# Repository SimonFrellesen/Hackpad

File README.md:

# Hackpad
This is my first ever project, it has taken me alot of time, but i finally think im done!
Its a Hackpad with inspiration from the Hackpad guide in Hackclub Blueprint.
Ive added an OLED and 2 SK6812 LEDs.

I made this project to learn and get experience. I love learning about things like PCB design and CAD design. Im interested in making more projects.

I want to give the keybinds some functions, which i havent decided yet. Probably Copy Paste and Back, and i want the LEDS to light up when i click any of the keybinds. The OLED is a starting screen.

Case:

Schematic:

PCB:

BOM

Microcontroller,1,Seeed XIAO RP2040, 3,9$ 
https://www.seeedstudio.com/XIAO-RP2040-v1-0-p-5026.html

Switches,3,MX Mechanical Switches, 3,54$
https://prototypist.net/products/in-stock-cherry-petal-switches-mx2a-10-pack?

Keycaps,3,DSA Blank Keycaps RED, 2,95$
https://spkeyboards.com/products/sp-dsa-1-space?_pos=2&_sid=1517b3abf&_ss=r

LEDs,2,SK6812 MINI-E,6,82 $
https://www.fruugo.dk/50pcs-sk6812-mini-e-rgb-similar-with-ws2812b-sk6812-3228-pixel-led-chip-individually-addressable-full-color-dc5v/p-463377372-975161187?language=en&ac=google&utm_source=google&utm_medium=paid&gclsrc=aw.ds&gad_source=1&gad_campaignid=22754370664&gclid=Cj0KCQiA4pvMBhDYARIsAGfgwvwNpXvtsZomRVqGYj1da2fajGKmsTNVzbFB5r3mlnLZWW9GODhXgWoaAosWEALw_wcB

Display,1,0.91in I2C OLED, 1,14 US$
https://www.alibaba.com/pla/091-Inch-OLED-Display-12832-Module_1601269142088.html?mark=google_shopping&biz=pla&searchText=lcd+modules&product_id=1601269142088&pcy=dk_en&src=sem_ggl&field=UG&from=sem_ggl&cmpgn=22700597011&adgrp=180785828586&fditm=&tgt=pla-295818637131&locintrst=&locphyscl=1005307&mtchtyp=&ntwrk=g&device=c&dvcmdl=&creative=759400368396&plcmnt=&plcmntcat=&aceid=&position=&gad_source=1&gad_campaignid=22700597011&gclid=Cj0KCQiA4pvMBhDYARIsAGfgwvx1X7AYZ3_Su9_hLzb9Zzgr-tyjhehcAmzHDxJittwtxviYdVgbd_4aAgNfEALw_wcB

PCB, 2$ print
https://cart.jlcpcb.com/quote?stencilLayer=2&stencilWidth=100&stencilLength=100&stencilCounts=5&plateType=1&spm=Jlcpcb.Homepage.1010

Total, 21,26$

3D printed case

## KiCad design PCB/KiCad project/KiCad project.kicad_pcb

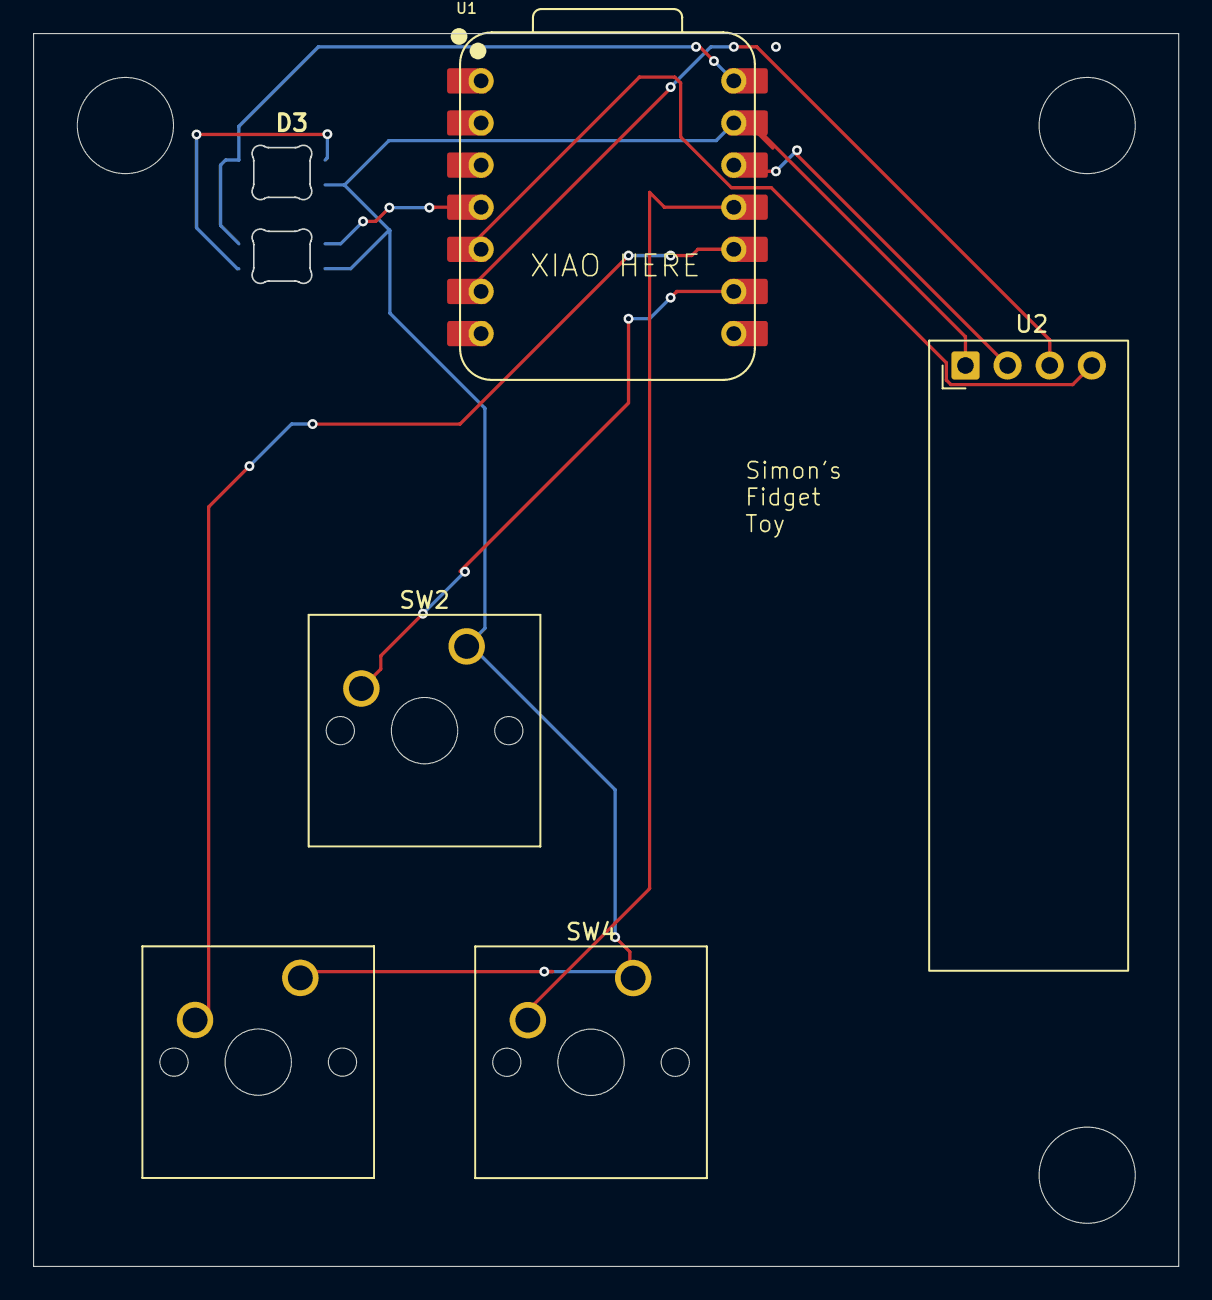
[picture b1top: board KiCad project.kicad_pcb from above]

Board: 2 copper layers, 69.0 x 74.3 mm, 7 parts (0 on the bottom side), 10 nets.

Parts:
D3, D4: SK6812MINI-E; SK6812MINI-E_fixed
SW2, SW3, SW4: SW_Push; SW_Cherry_MX_1.00u_PCB
U1: XIAO-RP2040-DIP
U2: OLED_0.91_128x32

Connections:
+5V: D3.1 (VDD), D4.1 (VDD), U1.14 (VBUS)
GND: D3.3 (VSS), D4.3 (VSS), SW2.1, SW3.1, SW4.1, U1.13 (GND), U2.1 (GND)
unnamed: D3.4 (DIN), D4.2 (DOUT)
unnamed: D4.4 (DIN), U1.4 (GPIO29/ADC3/A3)
unnamed: U1.12 (3V3), U2.2 (VCC)
unnamed: SW2.2, U1.9 (GPIO2/SCK)
unnamed: SW4.2, U1.11 (GPIO3/MOSI)
unnamed: SW3.2, U1.10 (GPIO4/MISO)
unnamed: U1.5 (GPIO6/SDA), U2.4 (SDA)
unnamed: U1.6 (GPIO7/SCL), U2.3 (SCL)

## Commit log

2026-01-30 Update README with project details and specifications
    Added project description, specifications, and images.
2026-01-30 Update README with images for case and PCB
    Added images for case, schematic, and PCB sections.
2026-01-30 Update README with BOM specifications and images
    Added specifications for BOM and case images.
2026-01-30 Update README with project specifications
    Add project specifications and BOM details
2026-02-07 Remove KiCad project job configuration file
2026-02-07 Remove duplicate keycap link from README
    Removed duplicate keycap link for clarity.
2026-02-07 Update README with project features and intentions
    Added details about keybind functions and OLED usage.
2026-02-08 Update README to clarify project features
    Removed mention of the case design for easier access.
2026-02-11 Update README with .stp and .step file explanation
    Clarified that .stp and .step files are the same 3D file format.
2026-02-12 Update images and add BOM section in README
2026-02-15 Remove duplicate PCB image from README
2026-02-15 Fix component prices and links in README
    Updated component list with corrected prices and links.
2026-02-15 Adjust prices in README for components
    Updated prices for switches, keycaps, and total cost.
2026-03-01 Revise README with project title and description
    Updated project title and improved introduction text.
2026-03-08 Add images to README
    Added two new images to the README file.
